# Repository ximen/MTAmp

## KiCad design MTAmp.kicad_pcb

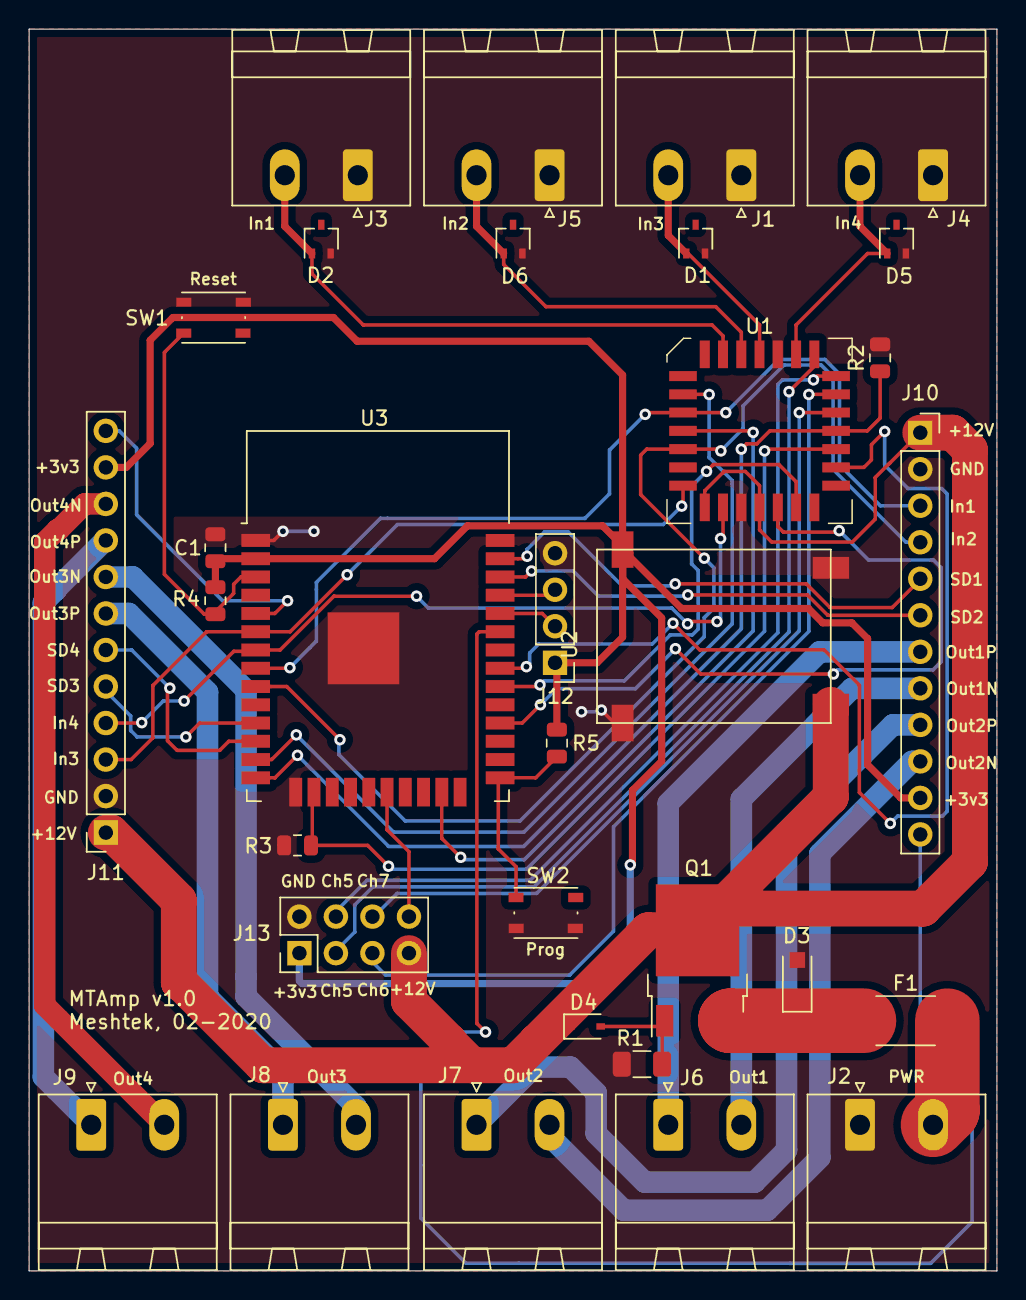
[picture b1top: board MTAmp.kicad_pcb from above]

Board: 2 copper layers, 67.3 x 86.4 mm, 32 parts (0 on the bottom side), 44 nets.

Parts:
C1: 10u; C_0805_2012Metric
D1, D2, D5, D6: SP0502BAJT; SOT-323_SC-70
D3: SMF26CA; D_SOD-123F
D4: BZT52C22S; D_SOD-323
F1: 24E1300A; Fuse_2512_6332Metric
J1: IN3; PhoenixContact_MSTBA_2,5_2-G-5,08_1x02_P5.08mm_Horizontal
J2: PWR; PhoenixContact_MSTBA_2,5_2-G-5,08_1x02_P5.08mm_Horizontal
J3: IN1; PhoenixContact_MSTBA_2,5_2-G-5,08_1x02_P5.08mm_Horizontal
J4: IN4; PhoenixContact_MSTBA_2,5_2-G-5,08_1x02_P5.08mm_Horizontal
J5: IN2; PhoenixContact_MSTBA_2,5_2-G-5,08_1x02_P5.08mm_Horizontal
J6: OUT1; PhoenixContact_MSTBA_2,5_2-G-5,08_1x02_P5.08mm_Horizontal
J7: OUT2; PhoenixContact_MSTBA_2,5_2-G-5,08_1x02_P5.08mm_Horizontal
J8: OUT3; PhoenixContact_MSTBA_2,5_2-G-5,08_1x02_P5.08mm_Horizontal
J9: OUT4; PhoenixContact_MSTBA_2,5_2-G-5,08_1x02_P5.08mm_Horizontal
J10: AMP1; PinSocket_1x12_P2.54mm_Vertical
J11: AMP2; PinSocket_1x12_P2.54mm_Vertical
J12: PROG; PinHeader_1x04_P2.54mm_Vertical
J13: BT; PinHeader_2x04_P2.54mm_Vertical
Q1: AOD403; TO-252-2
R1: 100k; R_1206_3216Metric
R2, R3, R4, R5: 10k; R_0805_2012Metric
SW1, SW2: SW_Push; SW_Push_1P1T_NO_Vertical_Wuerth_434133025816
U1: MT8806AP; PLCC-28
U2: MTDCDC
U3: ESP32-WROOM-32

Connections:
+3V3: C1.1, J10.11, J11.11, J12.1, J13.1, R4.1, R5.1, U2.3, U3.2
+12V: D4.1, J10.1, J11.1, J13.7, Q1.2, U1.12, U1.15, U2.1
CONNECTED1: J10.12, U3.33
CONNECTED2: J11.12, U3.5
CONNECTED_BT: J13.8, U3.20
GNDA: C1.2, D1.2, D2.2, D3.2, D5.2, D6.2, J1.1, J2.1, J3.1, J4.1, J5.1, J10.2, J11.2, J12.4, J13.2, R1.2, R2.2, R3.2, SW1.1, SW2.2, U1.14, U1.28, U2.2, U3.1, U3.15, U3.38, U3.39
MT_AX0: U1.8, U3.23
MT_AY0: U1.16, U3.28
MT_AY1: U1.17, U3.30
MT_AY2: U1.20, U3.31
MT_Data: U1.6, U3.13
MT_In1: D2.1, J3.2, U1.3
MT_In2: D6.1, J5.2, U1.2
MT_In3: D1.1, J1.2, U1.1
MT_In4: D5.1, J4.2, U1.27
MT_In5: J13.3, U1.26
MT_In6: J13.4, U1.25
MT_In7: J13.5, U1.24
MT_In8: J13.6, U1.23
MT_Out1: J10.3, U1.7, U3.8
MT_Out2: J10.4, U1.9, U3.9
MT_Out3: J11.3, U1.11, U3.6
MT_Out4: J11.4, U1.13, U3.7
MT_Reset: R2.1, U1.22, U3.14
MT_STB: R3.1, U1.21, U3.16
unnamed: D3.1, F1.1, Q1.3
unnamed: D4.2, Q1.1, R1.1
unnamed: F1.2, J2.2
unnamed: R4.2, SW1.2, U3.3
unnamed: R5.2, SW2.1, U3.25
Out1N: J6.2, J10.8
Out1P: J6.1, J10.7
Out2N: J7.2, J10.10
Out2P: J7.1, J10.9
Out3N: J8.2, J11.8
Out3P: J8.1, J11.7
Out4N: J9.2, J11.10
Out4P: J9.1, J11.9
RX: J12.2, U3.34
SD1: J10.5, U3.37
SD2: J10.6, U3.36
SD3: J11.5, U3.11
SD4: J11.6, U3.12
TX: J12.3, U3.35

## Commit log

2020-02-12 Initial Main board
2020-02-16 PSU and connectors added
2020-02-20 PCB created
2020-02-23 Main PCB traced
2020-02-23 Added some text on PCB
